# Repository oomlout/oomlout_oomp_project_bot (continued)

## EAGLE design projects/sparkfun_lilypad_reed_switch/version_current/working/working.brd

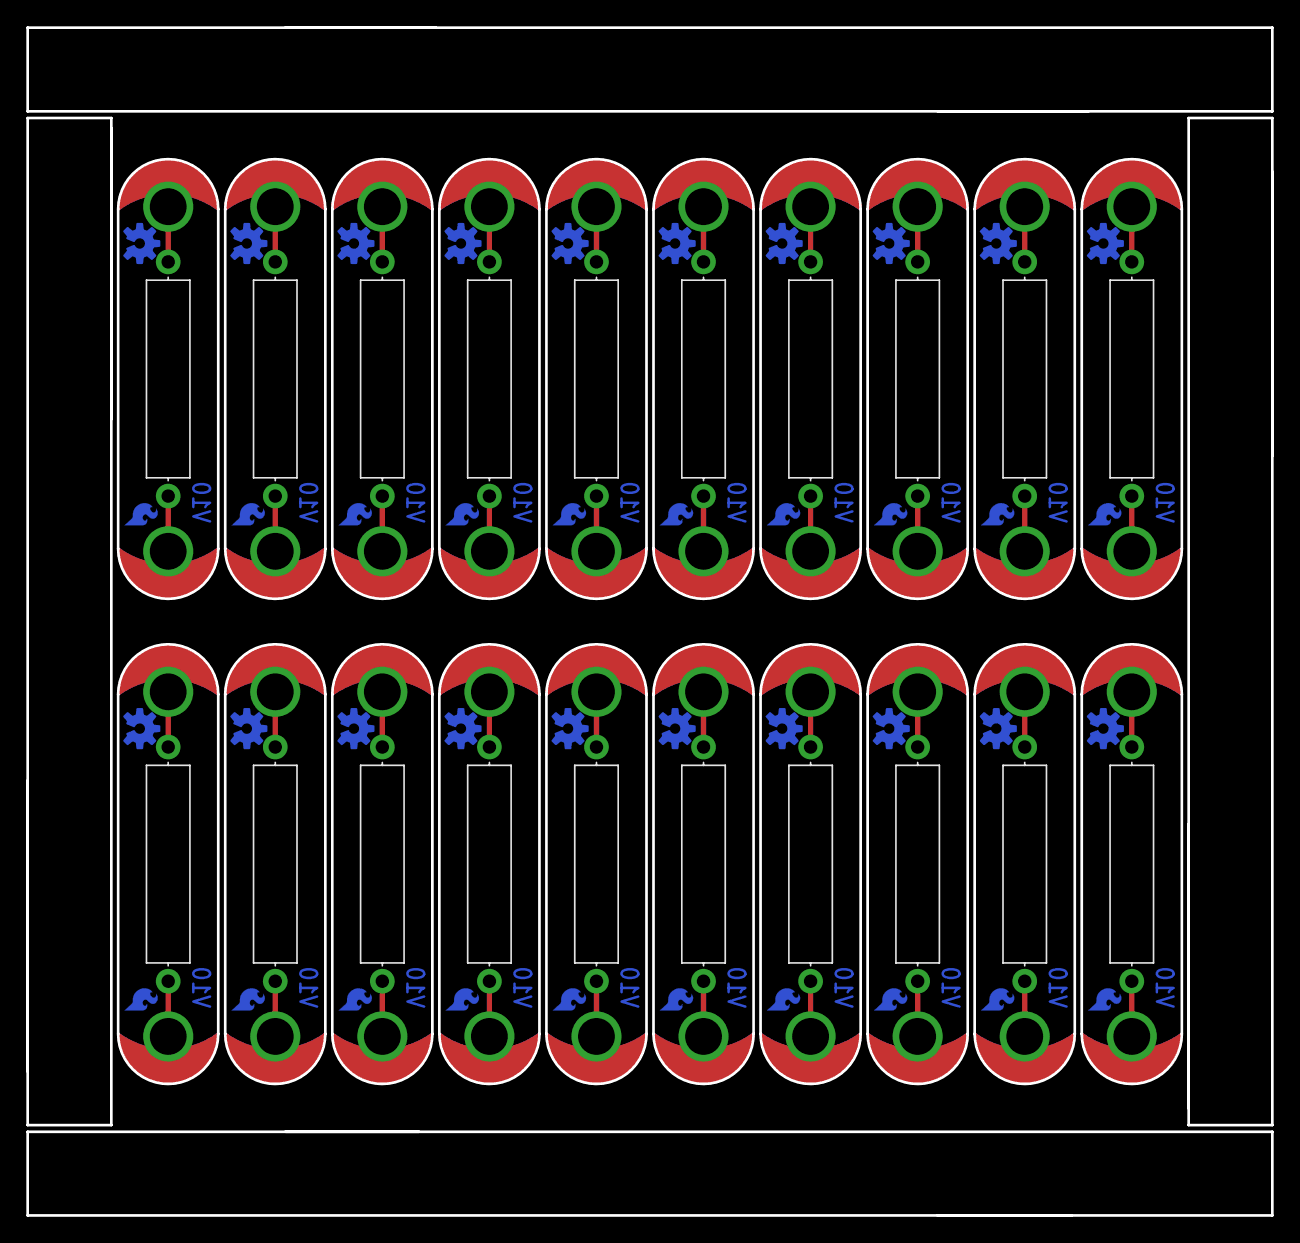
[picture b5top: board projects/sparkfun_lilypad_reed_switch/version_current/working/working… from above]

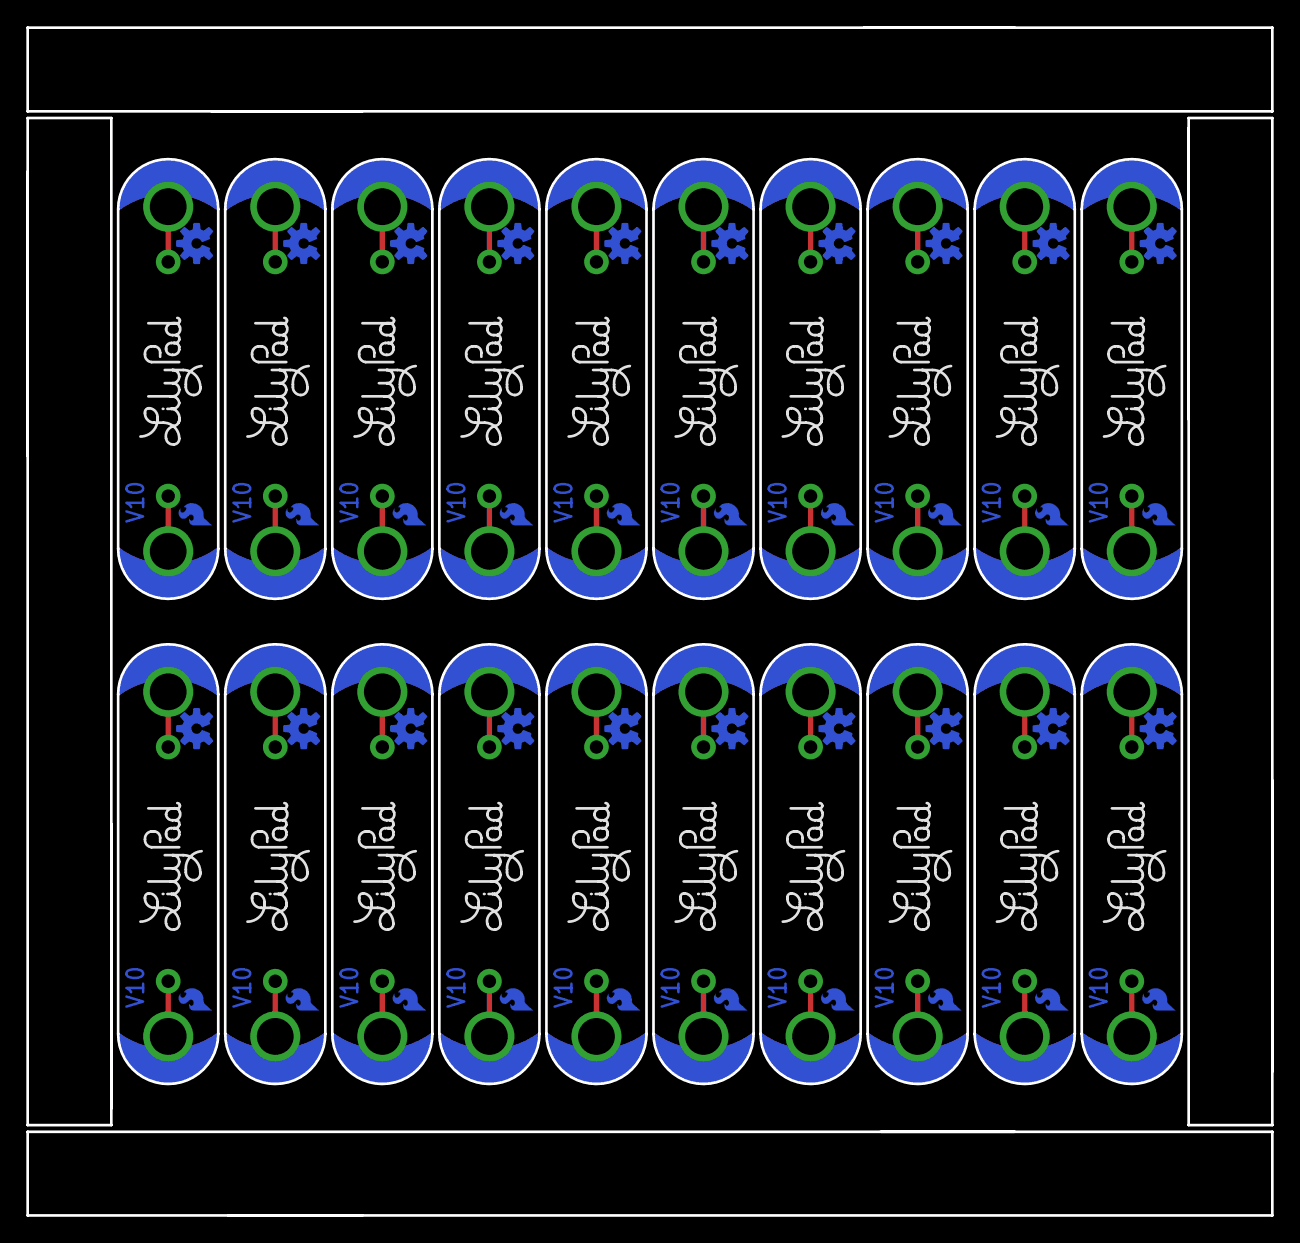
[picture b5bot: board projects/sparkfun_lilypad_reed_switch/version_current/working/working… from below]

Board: 2 copper layers, 94.5 x 90.2 mm, 120 parts (60 on the bottom side), 40 nets.

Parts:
LOGO1, LOGO3, LOGO5, LOGO7, LOGO9, LOGO11, LOGO13, LOGO15, LOGO17, LOGO19, LOGO21, LOGO23, LOGO25, LOGO27, LOGO29, LOGO31, LOGO33, LOGO35, LOGO37, LOGO39: OSHW-LOGOS-COPPER; OSHW-LOGO-S_COPPER
LOGO2, LOGO4, LOGO6, LOGO8, LOGO10, LOGO12, LOGO14, LOGO16, LOGO18, LOGO20, LOGO22, LOGO24, LOGO26, LOGO28, LOGO30, LOGO32, LOGO34, LOGO36, LOGO38, LOGO40: SFE_LOGO_FLAME.1COP; SFE_LOGO_FLAME_COPPER_.1
S1, S2, S3, S4, S5, S6, S7, S8, S9, S10, S11, S12, S13, S14, S15, S16, S17, S18, S19, S20: REED; REED_SWITCH_PLASTIC
SLIDEOFF, SLIDEOFF1, SLIDEOFF2, SLIDEOFF3, SLIDEOFF4, SLIDEOFF5, SLIDEOFF6, SLIDEOFF7, SLIDEOFF8, SLIDEOFF9, SLIDEOFF10, SLIDEOFF11, SLIDEOFF12, SLIDEOFF13, SLIDEOFF14, SLIDEOFF15, SLIDEOFF16, SLIDEOFF17, SLIDEOFF18, SLIDEOFF19: SEWTAP8; PETAL-MEDIUM-2SIDE
SLIDEON, SLIDEON1, SLIDEON2, SLIDEON3, SLIDEON4, SLIDEON5, SLIDEON6, SLIDEON7, SLIDEON8, SLIDEON9, SLIDEON10, SLIDEON11, SLIDEON12, SLIDEON13, SLIDEON14, SLIDEON15, SLIDEON16, SLIDEON17, SLIDEON18, SLIDEON19: SEWTAP8; PETAL-MEDIUM-2SIDE
U$1, U$2, U$3, U$4, U$5, U$6, U$7, U$8, U$9, U$10, U$11, U$12, U$13, U$14, U$15, U$16, U$17, U$18, U$19, U$20: LOGO-LPLP; LOGO-LILYPAD

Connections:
unnamed: S1.P$2, SLIDEOFF.1
unnamed: S1.P$1, SLIDEON.1
unnamed: S2.P$2, SLIDEOFF1.1
unnamed: S2.P$1, SLIDEON1.1
unnamed: S3.P$2, SLIDEOFF2.1
unnamed: S3.P$1, SLIDEON2.1
unnamed: S4.P$2, SLIDEOFF3.1
unnamed: S4.P$1, SLIDEON3.1
unnamed: S5.P$2, SLIDEOFF4.1
unnamed: S5.P$1, SLIDEON4.1
unnamed: S6.P$2, SLIDEOFF5.1
unnamed: S6.P$1, SLIDEON5.1
unnamed: S7.P$2, SLIDEOFF6.1
unnamed: S7.P$1, SLIDEON6.1
unnamed: S8.P$2, SLIDEOFF7.1
unnamed: S8.P$1, SLIDEON7.1
unnamed: S9.P$2, SLIDEOFF8.1
unnamed: S9.P$1, SLIDEON8.1
unnamed: S10.P$2, SLIDEOFF9.1
unnamed: S10.P$1, SLIDEON9.1
unnamed: S11.P$2, SLIDEOFF10.1
unnamed: S11.P$1, SLIDEON10.1
unnamed: S12.P$2, SLIDEOFF11.1
unnamed: S12.P$1, SLIDEON11.1
unnamed: S13.P$2, SLIDEOFF12.1
unnamed: S13.P$1, SLIDEON12.1
unnamed: S14.P$2, SLIDEOFF13.1
unnamed: S14.P$1, SLIDEON13.1
unnamed: S15.P$2, SLIDEOFF14.1
unnamed: S15.P$1, SLIDEON14.1
unnamed: S16.P$2, SLIDEOFF15.1
unnamed: S16.P$1, SLIDEON15.1
unnamed: S17.P$2, SLIDEOFF16.1
unnamed: S17.P$1, SLIDEON16.1
unnamed: S18.P$2, SLIDEOFF17.1
unnamed: S18.P$1, SLIDEON17.1
unnamed: S19.P$2, SLIDEOFF18.1
unnamed: S19.P$1, SLIDEON18.1
unnamed: S20.P$2, SLIDEOFF19.1
unnamed: S20.P$1, SLIDEON19.1

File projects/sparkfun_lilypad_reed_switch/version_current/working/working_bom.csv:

Row,Description,Part,References,Value,Footprint,Quantity Per PCB,Status,Datasheet
1,,FRAME-LETTER,FRAME1,FRAME-LETTER,CREATIVE_COMMONS,1, ,
2,,OSHW-LOGOS-COPPER,LOGO1,OSHW-LOGOS-COPPER,OSHW-LOGO-S_COPPER,1, ,
3,,SFE_LOGO_FLAME.1COP,LOGO2,SFE_LOGO_FLAME.1COP,SFE_LOGO_FLAME_COPPER_.1,1, ,
4,,SWITCH-MOMENTARY-2PTH_REED2,S1,SWITCH-MOMENTARY-2PTH_REED2,REED_SWITCH_PLASTIC,1, ,
5,,SEWTAP8,SLIDEOFF0 SLIDEON0,SEWTAP8,PETAL-MEDIUM-2SIDE,2, ,
6,,LOGO-LPLP,U$1,LOGO-LPLP,LOGO-LILYPAD,1, ,





Project info:
Schematic:,working
Variant:,default
Revision:,
Date:,2023-08-06_12-56-04
KiCad Version:,7.0.6-7.0.6~ubuntu22.04.1
Statistics:
Component Groups:,6
Component Count:,7 (0 SMD/ 0 THT)
Fitted Components:,7 (0 SMD/ 0 THT)
Number of PCBs:,1
Total Components:,7

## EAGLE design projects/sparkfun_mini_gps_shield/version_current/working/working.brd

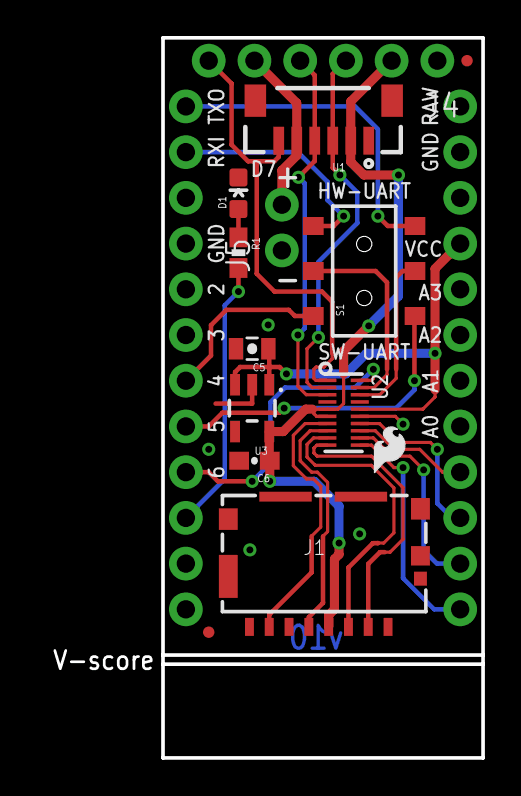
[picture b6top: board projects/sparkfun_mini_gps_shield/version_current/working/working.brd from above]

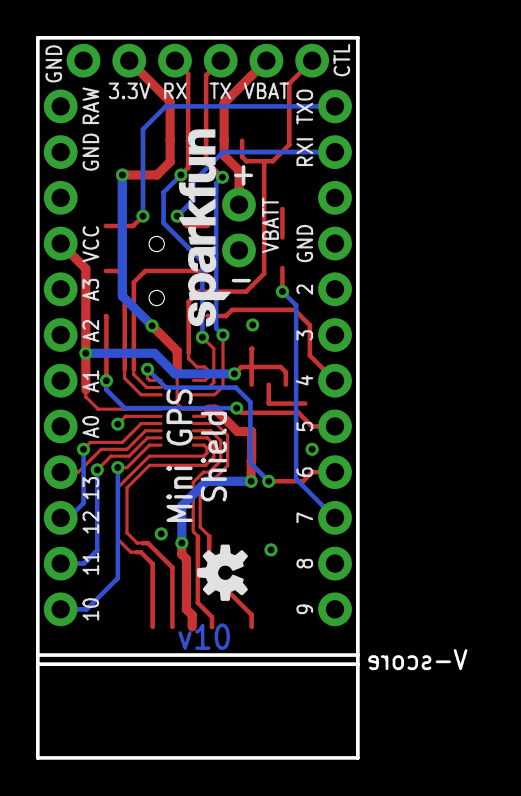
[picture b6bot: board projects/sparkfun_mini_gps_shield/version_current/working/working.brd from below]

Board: 2 copper layers, 17.8 x 40.0 mm, 19 parts (2 on the bottom side), 24 nets.

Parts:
C5: 1.0uF; 0805-CAP
C6: 2.2uF; 0603-CAP
D1: BLUE; LED-0603
FD1, FD2: FIDUCIALUFIDUCIAL; MICRO-FIDUCIAL
FRAME1: FRAME-LETTER; CREATIVE_COMMONS
J1: MICROSD_TINY
J2, J3: 1X12_NO_SILK
J4: 1X06_NO_SILK
J5: 1X02_NO_SILK
LOGO1: OSHW-LOGOS; OSHW-LOGO-S
LOGO3: SFE_LOGO_FLAME.1_INCH; SFE_LOGO_FLAME_.1
LOGO4: SFE_LOGO_NAME.1_INCH; SFE_LOGO_NAME_.1
R1: 470; 0603-RES
S1: DPDT; AYZ0202
U1: GP735
U2: TXB0108; UFDFN-20
U3: AP2112K-3.3V; SOT23-5

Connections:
3.3V: C6.1, J1.4, J4.2, U1.2, U2.5, U2.6, U3.5
4: J2.6, S1.1
5: J2.5, S1.4
6: J2.4, U2.20
7: J2.3, R1.2
10: J3.1, U2.11
11: J3.2, U2.12
12: J3.3, U2.14
13: J3.4, U2.13
GND: C5.2, C6.2, D1.C, J1.6, J1.GND1, J1.GND2, J1.GND3, J1.GND4, J1.GND5, J1.GND6, J2.9, J3.11, J4.1, J5.1, U1.1, U2.15, U3.2
GPS_CTRL: J4.6, U1.6, U2.1
GPS_RX: J4.4, U1.4, U2.3
GPS_TX: J4.3, U1.3, U2.2
unnamed: D1.A, R1.1
RX: S1.2, U2.19
RX/0: J2.11, S1.3
SD_CS: J1.2, U2.10
SD_DI: J1.3, U2.9
SD_DO: J1.7, U2.7
SD_SCK: J1.5, U2.8
TX: S1.5, U2.18
TX/1: J2.12, S1.6
VCC: C5.1, J3.9, U2.16, U3.1, U3.3
V_BATT: J4.5, J5.2, U1.5

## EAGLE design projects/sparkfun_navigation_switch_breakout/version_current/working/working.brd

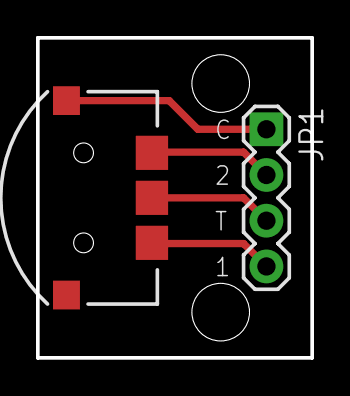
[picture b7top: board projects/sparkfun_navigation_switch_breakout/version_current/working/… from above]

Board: 2 copper layers, 15.2 x 17.8 mm, 3 parts (1 on the bottom side), 4 nets.

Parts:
JP1: 1X04
JP2: NAV_SWITCH
U$1: LOGO-SFESK; SFE-LOGO-FLAME

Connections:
unnamed: JP1.1, JP2.C
unnamed: JP1.2, JP2.2
unnamed: JP1.3, JP2.T
unnamed: JP1.4, JP2.1
